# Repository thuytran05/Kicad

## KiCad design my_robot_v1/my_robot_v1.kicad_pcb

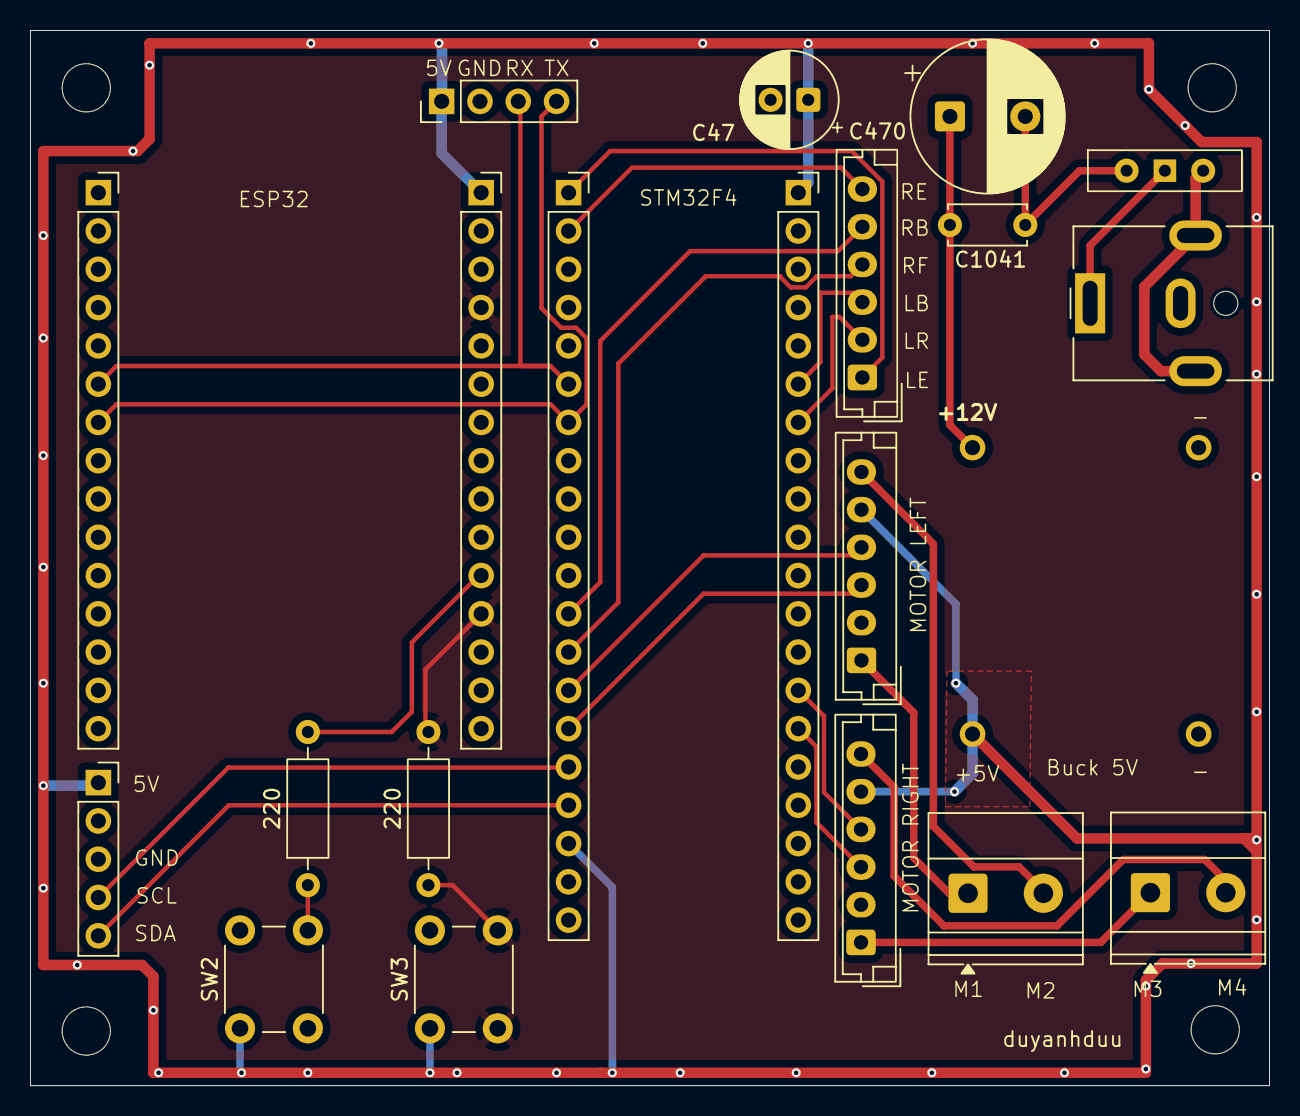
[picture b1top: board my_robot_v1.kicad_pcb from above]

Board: 2 copper layers, 82.2 x 70.0 mm, 21 parts (0 on the bottom side), 25 nets.

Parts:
12V_POWER1: Jack-DC; BarrelJack_CUI_PJ-063AH_Horizontal
220, 220#2: R; R_Axial_DIN0207_L6.3mm_D2.5mm_P10.16mm_Horizontal
Buck1: Conn_01x04; test1
C47: C; CP_Radial_D6.3mm_P2.50mm
C470: C; CP_Radial_D10.0mm_P5.00mm
C1041: C; C_Disc_D5.0mm_W2.5mm_P5.00mm
Debug: Conn_01x04; PinHeader_1x04_P2.54mm_Vertical
ESP32_PIN1, ESP32_PIN2: Conn_01x15_Socket; PinSocket_1x15_P2.54mm_Vertical
IMU1: Conn_01x05_Socket; PinSocket_1x05_P2.54mm_Vertical
L298N_INPUT1: Conn_01x06_Socket; JST_EH_B6B-EH-A_1x06_P2.50mm_Vertical
LEFT_MOTOR1: Conn_01x06_Socket; JST_EH_B6B-EH-A_1x06_P2.50mm_Vertical
ML1: Conn_01x02; TerminalBlock_Phoenix_MKDS-1,5-2_1x02_P5.00mm_Horizontal
MR1: Conn_01x02; TerminalBlock_Phoenix_MKDS-1,5-2_1x02_P5.00mm_Horizontal
RIGHT_MOTOR1: Conn_01x06_Socket; JST_EH_B6B-EH-A_1x06_P2.50mm_Vertical
STM32_PIN1, STM32_PIN2: Conn_01x20_Socket; PinSocket_1x20_P2.54mm_Vertical
SW1: SW_SPST; SW_Slide-03_Wuerth-WS-SLTV_10x2.5x6.4_P2.54mm
SW2, SW3: SW_Push; SW_PUSH_6mm_H5mm

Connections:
3V3: ESP32_PIN1.1, IMU1.2, STM32_PIN1.20, STM32_PIN2.3
5V: Buck1.4, C47.1, Debug.1, ESP32_PIN2.1, IMU1.1, LEFT_MOTOR1.5, RIGHT_MOTOR1.5, STM32_PIN1.18, STM32_PIN2.1, SW2.1, SW3.1
12V: Buck1.2, C470.1, C470.2, C1041.1, C1041.2, SW1.2 (B)
C1: LEFT_MOTOR1.4, STM32_PIN1.14
C2: LEFT_MOTOR1.3, STM32_PIN1.15
C3: RIGHT_MOTOR1.4, STM32_PIN2.14
C4: RIGHT_MOTOR1.3, STM32_PIN2.15
D12: 220.2, ESP32_PIN2.4, ESP32_PIN2.12, SW3.2
D13: 220#2.2, ESP32_PIN2.3, ESP32_PIN2.11, SW2.2
GND: 12V_POWER1.2, 220.1, 220#2.1, Buck1.1, Buck1.3, C47.2, Debug.2, ESP32_PIN1.2, ESP32_PIN2.2, IMU1.3, LEFT_MOTOR1.2, RIGHT_MOTOR1.2, STM32_PIN1.19, STM32_PIN2.2
L_BACK: L298N_INPUT1.3, STM32_PIN2.6
L_FORW: L298N_INPUT1.2, STM32_PIN2.7
L_enablePin: L298N_INPUT1.1, STM32_PIN1.1
M1: LEFT_MOTOR1.1, ML1.1
M2: LEFT_MOTOR1.6, ML1.2
M3: MR1.1, RIGHT_MOTOR1.1
M4: MR1.2, RIGHT_MOTOR1.6
unnamed: 12V_POWER1.1, SW1.1 (A)
RX_PIN: Debug.3, ESP32_PIN1.6, STM32_PIN1.6
R_BACK: L298N_INPUT1.5, STM32_PIN1.12
R_FORW: L298N_INPUT1.4, STM32_PIN1.13
R_enablePin: L298N_INPUT1.6, STM32_PIN1.2
SCL: IMU1.4, STM32_PIN1.16
SDA: IMU1.5, STM32_PIN1.17
TX_PIN: Debug.4, ESP32_PIN1.7, STM32_PIN1.7
